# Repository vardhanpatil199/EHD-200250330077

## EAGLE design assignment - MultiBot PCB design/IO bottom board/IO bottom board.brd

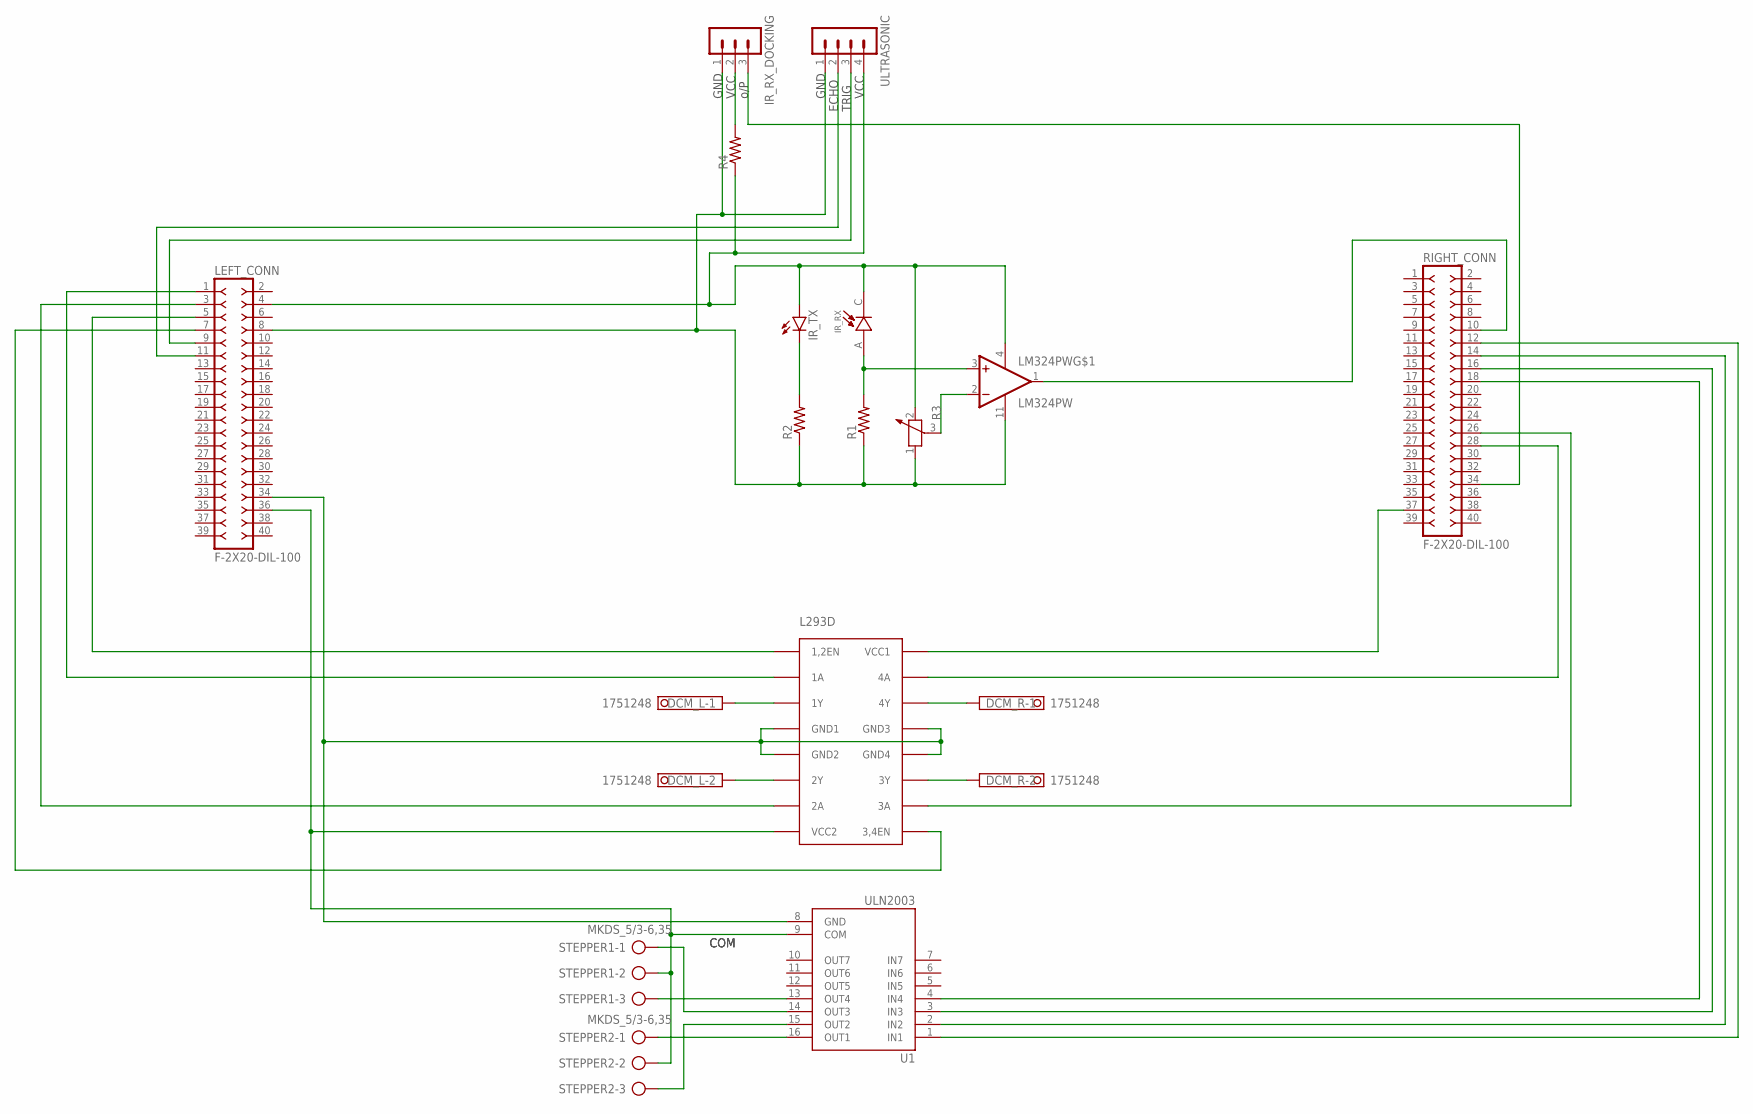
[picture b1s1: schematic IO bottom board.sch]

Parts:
DCM_L: 1751248
DCM_R: 1751248
IR_RX: BPV10; XDCR_BPV10
IR_RX_DOCKING: MA03-1
IR_TX: SFH482
L293D: L293D; DIL16
LEFT_CONN: F-2X20-DIL-100; DIL-100-2X20
LM324PW: LM324PW; SOP65P640X120-14N
R1, R2, R4: R-US_0204/5; 0204/5
R3: POTENTIOMETER_PT-10; PT-10
RIGHT_CONN: F-2X20-DIL-100; DIL-100-2X20
STEPPER1, STEPPER2: MKDS_5/3-6,35; MKDS_5/3-635
U1: ULN2003; DIP762W46P254L1969H533Q16
ULTRASONIC: MA04-1

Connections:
unnamed: DCM_L.1, L293D.3 (1Y)
unnamed: DCM_L.2, L293D.6 (2Y)
unnamed: DCM_R.1, L293D.14 (4Y)
unnamed: DCM_R.2, L293D.11 (3Y)
unnamed: LEFT_CONN.11, ULTRASONIC.2
unnamed: LEFT_CONN.9, ULTRASONIC.3
unnamed: IR_RX_DOCKING.2, R4.2
unnamed: L293D.16 (VCC1), RIGHT_CONN.37
unnamed: RIGHT_CONN.12, U1.1 (IN1)
unnamed: RIGHT_CONN.14, U1.2 (IN2)
unnamed: RIGHT_CONN.16, U1.3 (IN3)
unnamed: RIGHT_CONN.18, U1.4 (IN4)
unnamed: STEPPER2.1, U1.16 (OUT1)
unnamed: STEPPER2.3, U1.15 (OUT2)
unnamed: STEPPER1.1, U1.14 (OUT3)
unnamed: STEPPER1.3, U1.13 (OUT4)
unnamed: L293D.8 (VCC2), LEFT_CONN.36, STEPPER1.2, STEPPER2.2, U1.9 (COM)
unnamed: LM324PW.1 (OUT1), RIGHT_CONN.10
unnamed: L293D.4 (GND1), L293D.5 (GND2), L293D.12 (GND4), L293D.13 (GND3), LEFT_CONN.34, U1.8 (GND)
unnamed: IR_RX.C, IR_TX.A, LEFT_CONN.4, LM324PW.4 (VCC), R3.2, R4.1, ULTRASONIC.4
unnamed: IR_TX.K (C), R2.2
unnamed: IR_RX.A, LM324PW.3 (+IN1), R1.2
unnamed: LM324PW.2 (-IN1), R3.3
unnamed: L293D.1 (1,2EN), LEFT_CONN.5
unnamed: L293D.9 (3,4EN), LEFT_CONN.7
unnamed: IR_RX_DOCKING.1, LEFT_CONN.8, LM324PW.11 (GND), R1.1, R2.1, R3.1, ULTRASONIC.1
unnamed: IR_RX_DOCKING.3, RIGHT_CONN.34
unnamed: L293D.2 (1A), LEFT_CONN.1
unnamed: L293D.7 (2A), LEFT_CONN.3
unnamed: L293D.10 (3A), RIGHT_CONN.26
unnamed: L293D.15 (4A), RIGHT_CONN.28

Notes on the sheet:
GND
VCC
o/P
TRIG
ECHO
COM

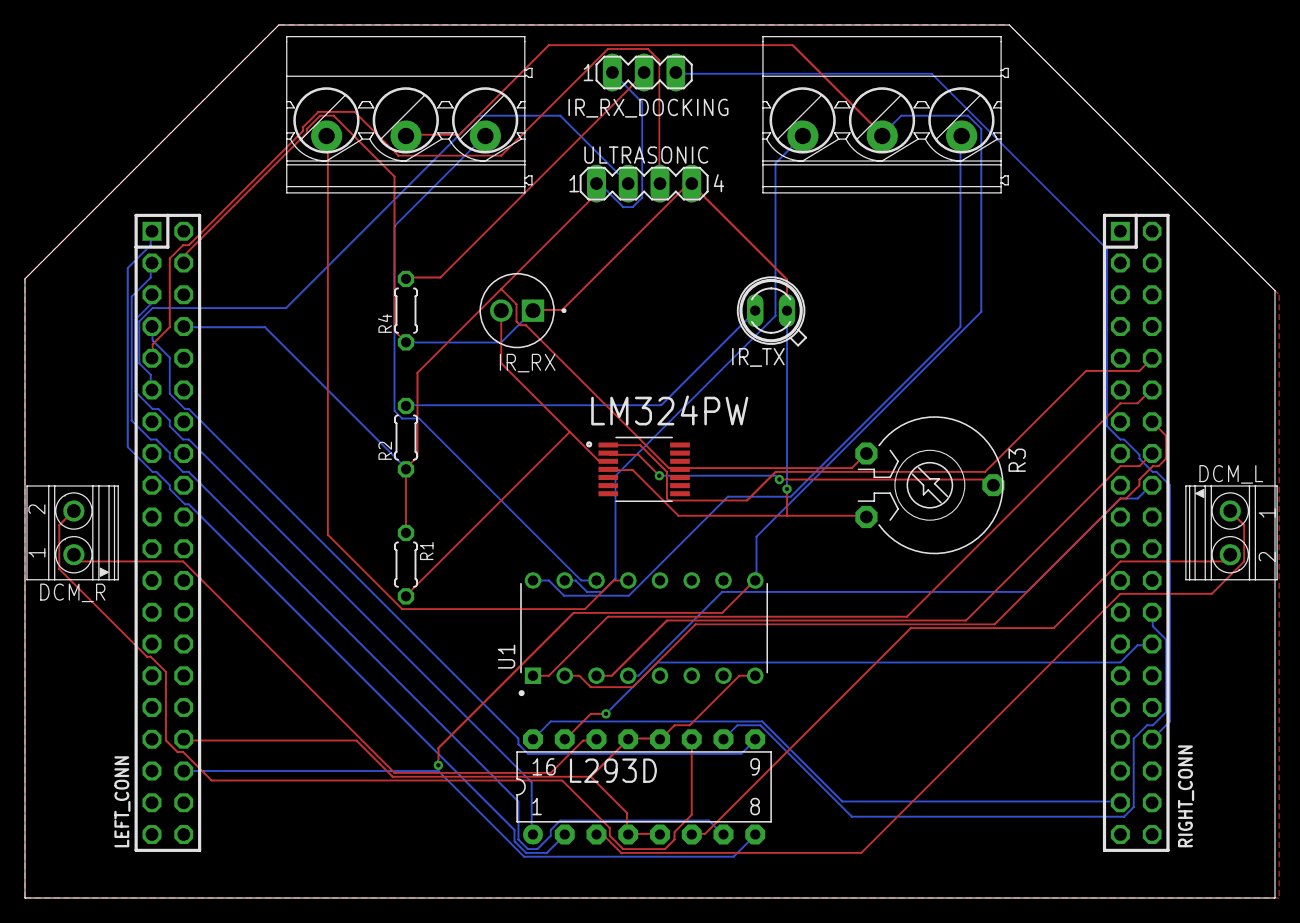
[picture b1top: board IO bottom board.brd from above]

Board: 2 copper layers, 100.0 x 69.8 mm, 17 parts (0 on the bottom side), 31 nets.

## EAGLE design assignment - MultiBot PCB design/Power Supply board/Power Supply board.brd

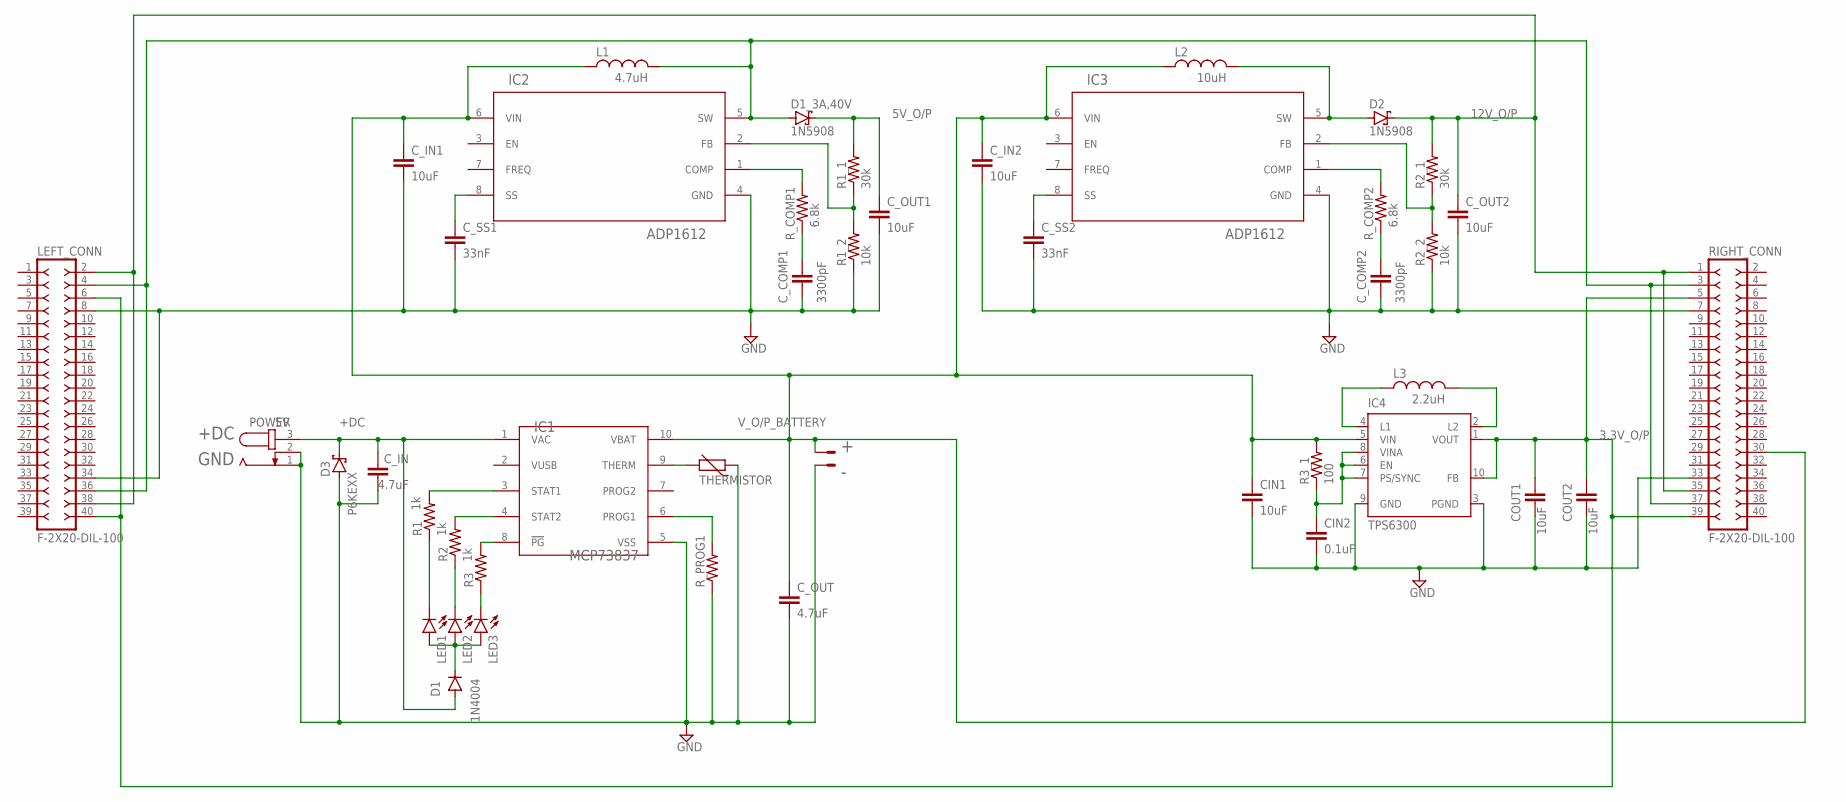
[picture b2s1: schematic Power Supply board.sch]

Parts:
BATT-CHARGING: JST-XH-02-PIN-ROUND-PAD; JST-XH-02-PACKAGE-ROUND-PAD
CIN1: 10uF; C025-024X044
CIN2: 0.1uF; C025-024X044
COUT1, COUT2: 10uF; C025-024X044
C_COMP1, C_COMP2: 3300pF; C025-024X044
C_IN: 4.7uF; C025-024X044
C_IN1, C_IN2: 10uF; C025-024X044
C_OUT: 4.7uF; C025-024X044
C_OUT1, C_OUT2: 10uF; C025-024X044
C_SS1, C_SS2: 33nF; C025-024X044
D1: 1N4004; DO41-10
D1_3A,40V, D2: 1N5908; C4111-15
D3: P6KEXX; CB417-15
IC1: MCP73837; MSOP10_MC_MCH
IC2, IC3: ADP1612; RM_8_ADI
IC4: TPS6300; DRC-S-PVSON-N10
L1: 4.7uH; 0204/7
L2: 10uH; 0204/7
L3: 2.2uH; 0204/7
LED1, LED2, LED3: LED3MM
LEFT_CONN: F-2X20-DIL-100; DIL-100-2X20
POWER: 5V; SPC4077
R1, R2, R3: 1k; 0204/7
R1_1, R2_1: 30k; 0204/7
R1_2, R2_2: 10k; 0204/7
R3_1: 100; 0204/7
RIGHT_CONN: F-2X20-DIL-100; DIL-100-2X20
R_COMP1, R_COMP2: 6.8k; 0204/7
R_PROG1: R-US_0204/7; 0204/7
THERMISTOR: THERMISTOR-5; R-5

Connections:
3.3V_O/P: COUT1.1, COUT2.1, IC4.1 (VOUT), IC4.10 (FB), LEFT_CONN.6, LEFT_CONN.40, RIGHT_CONN.5, RIGHT_CONN.39
5V_O/P: C_OUT1.1, D1_3A,40V.C, R1_1.2
12V_O/P: C_OUT2.1, D2.C, LEFT_CONN.2, LEFT_CONN.38, R2_1.2, RIGHT_CONN.1, RIGHT_CONN.35
+DC: C_IN.1, D1.A, D3.C, IC1.1 (VAC), POWER.3
GND: BATT-CHARGING.2, CIN1.2, CIN2.2, COUT1.2, COUT2.2, C_COMP1.2, C_COMP2.2, C_IN.2, C_IN1.2, C_IN2.2, C_OUT.2, C_OUT1.2, C_OUT2.2, C_SS1.2, C_SS2.2, D3.A, IC1.5 (VSS), IC2.4 (GND), IC3.4 (GND), IC4.3 (PGND), IC4.9 (GND), LEFT_CONN.8, LEFT_CONN.34, POWER.1, POWER.2, R1_2.1, R2_2.1, RIGHT_CONN.7, RIGHT_CONN.33, R_PROG1.1, THERMISTOR.1
unnamed: IC4.4 (L1), L3.1
unnamed: D1_3A,40V.A, IC2.5 (SW), L1.2, LEFT_CONN.4, LEFT_CONN.36, RIGHT_CONN.3, RIGHT_CONN.37
unnamed: IC2.2 (FB), R1_1.1, R1_2.2
unnamed: IC2.1 (COMP), R_COMP1.2
unnamed: C_COMP1.1, R_COMP1.1
unnamed: IC4.2 (L2), L3.2
unnamed: D2.A, IC3.5 (SW), L2.2
unnamed: IC1.6 (PROG1), R_PROG1.2
unnamed: IC3.2 (FB), R2_1.1, R2_2.2
unnamed: C_SS1.1, IC2.8 (SS)
unnamed: IC3.1 (COMP), R_COMP2.2
unnamed: C_COMP2.1, R_COMP2.1
unnamed: C_SS2.1, IC3.8 (SS)
unnamed: IC1.3 (STAT1), R1.2
unnamed: IC1.4 (STAT2), R2.2
unnamed: CIN2.1, IC4.6 (EN), IC4.7 (PS/SYNC), IC4.8 (VINA), R3_1.1
unnamed: IC1.8 (!PG), R3.2
unnamed: D1.C, LED1.A, LED2.A, LED3.A
unnamed: LED1.K (C), R1.1
unnamed: LED2.K (C), R2.1
unnamed: LED3.K (C), R3.1
unnamed: IC1.9 (THERM), THERMISTOR.2
V_O/P_BATTERY: BATT-CHARGING.1, CIN1.1, C_IN1.1, C_IN2.1, C_OUT.1, IC1.10 (VBAT), IC2.6 (VIN), IC3.6 (VIN), IC4.5 (VIN), L1.1, L2.1, R3_1.2, RIGHT_CONN.30

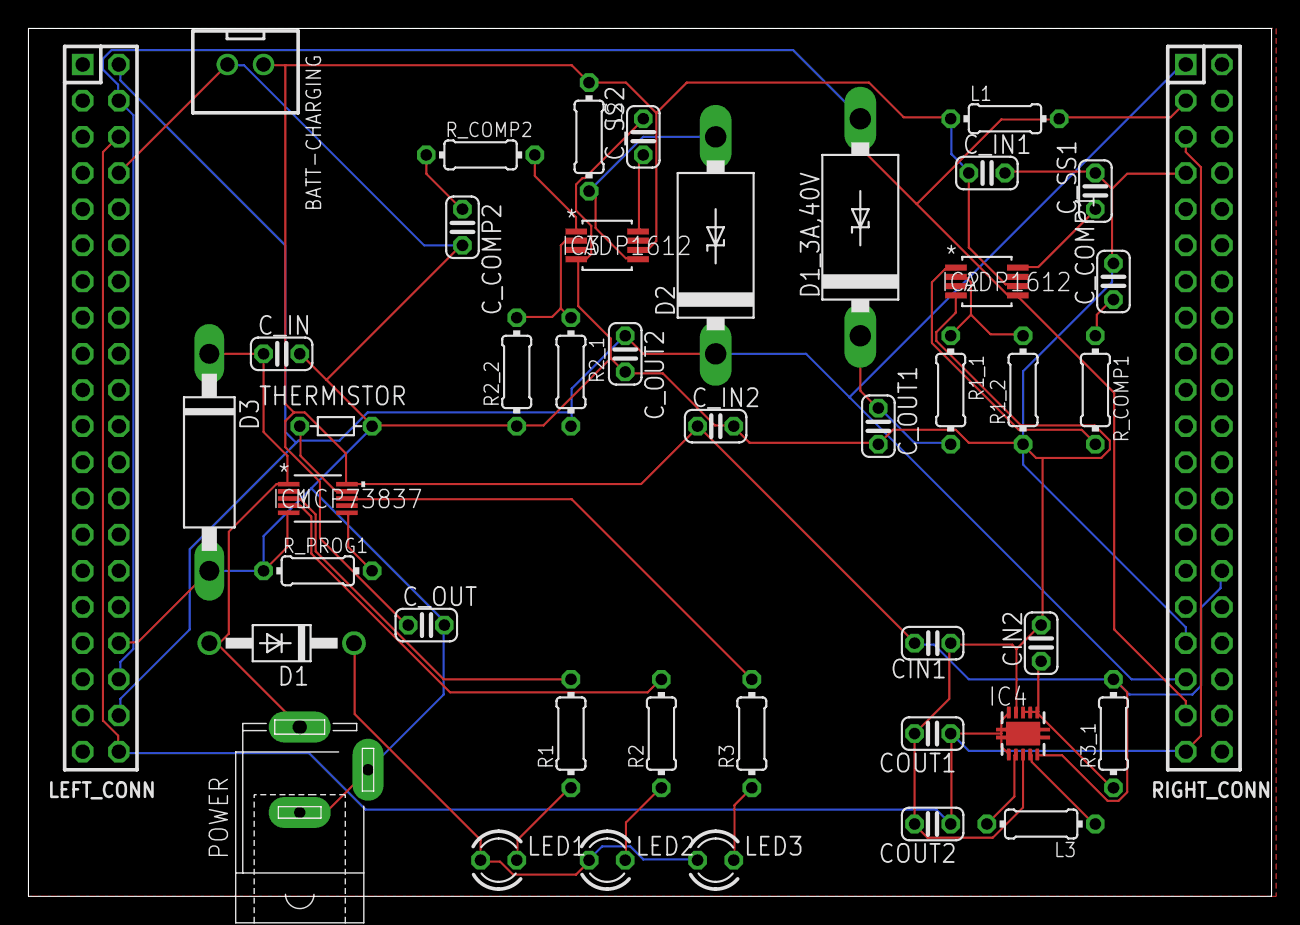
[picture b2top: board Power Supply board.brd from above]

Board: 2 copper layers, 87.3 x 61.0 mm, 44 parts (0 on the bottom side), 28 nets.

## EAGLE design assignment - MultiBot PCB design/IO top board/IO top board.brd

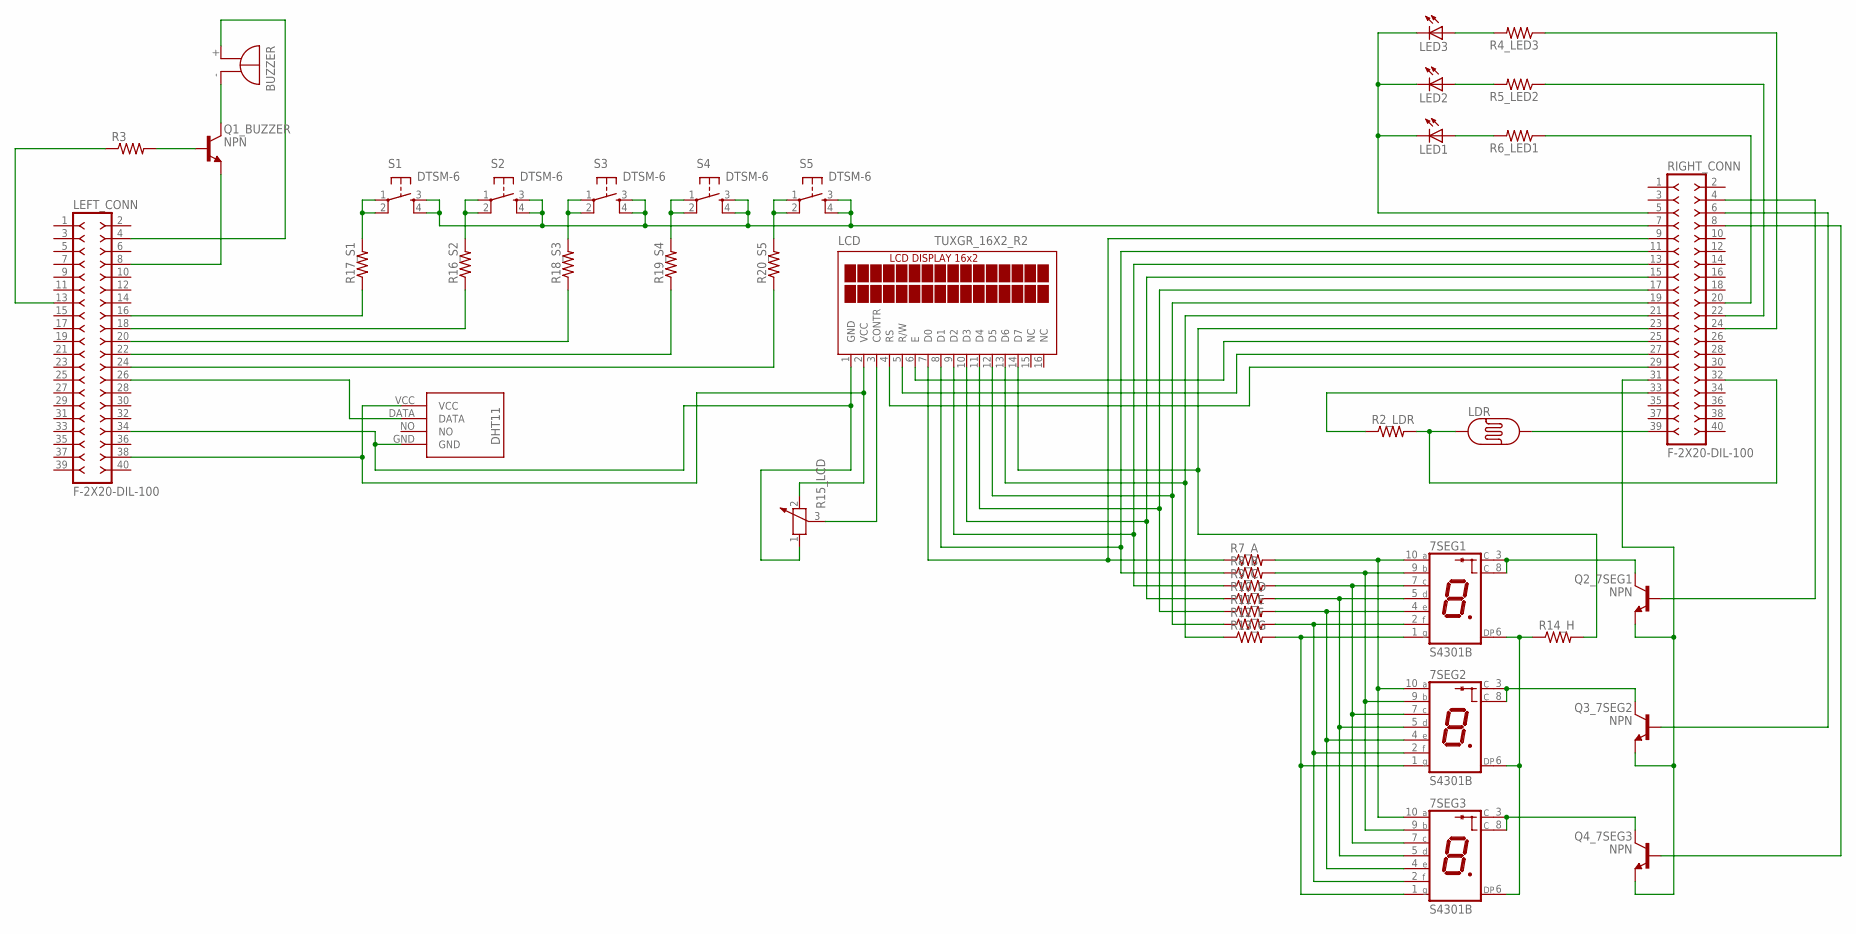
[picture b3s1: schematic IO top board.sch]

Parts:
7SEG1, 7SEG2, 7SEG3: S4301B
BUZZER: EB2209A
LCD: TUXGR_16X2_R2
LDR: PHOTOCELLONB; ON_BOARD
LED1, LED2, LED3: LED_ELD260; LED_LD260
LEFT_CONN: F-2X20-DIL-100; DIL-100-2X20
Q1_BUZZER, Q2_7SEG1, Q3_7SEG2, Q4_7SEG3: NPN; SC70
R2_LDR, R3, R4_LED3, R5_LED2, R6_LED1, R7_A, R8_B, R9_C, R10_D, R11_E, R12_F, R13_G, R14_H, R16_S2, R17_S1, R18_S3, R19_S4, R20_S5: R-US_0204/5; 0204/5
R15_LCD: POTENTIOMETER_PT-10; PT-10
RIGHT_CONN: F-2X20-DIL-100; DIL-100-2X20
S1, S2, S3, S4, S5: DTSM-6
U$1: DHT11-PION.

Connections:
unnamed: LDR.1, R2_LDR.2, RIGHT_CONN.32
unnamed: R2_LDR.1, RIGHT_CONN.33
unnamed: LDR.2, RIGHT_CONN.39
unnamed: LCD.2 (VCC), LEFT_CONN.38, R15_LCD.2, U$1.VCC
unnamed: LCD.1 (GND), LEFT_CONN.34, R15_LCD.1, U$1.GND
unnamed: LEFT_CONN.26, U$1.DATA
unnamed: Q1_BUZZER.2 (B), R3.2
unnamed: BUZZER.-, Q1_BUZZER.3 (C)
unnamed: BUZZER.+, LEFT_CONN.4
unnamed: LEFT_CONN.8, Q1_BUZZER.1 (E)
unnamed: LED1.A, R6_LED1.2
unnamed: LED2.A, R5_LED2.2
unnamed: LED3.A, R4_LED3.2
unnamed: LEFT_CONN.16, R17_S1.1
unnamed: LED1.K (C), LED2.K (C), LED3.K (C), RIGHT_CONN.5
unnamed: R4_LED3.1, RIGHT_CONN.24
unnamed: R5_LED2.1, RIGHT_CONN.22
unnamed: R6_LED1.1, RIGHT_CONN.20
unnamed: 7SEG1.6 (DP), 7SEG2.6 (DP), 7SEG3.6 (DP), R14_H.1
unnamed: 7SEG1.1 (G), 7SEG2.1 (G), 7SEG3.1 (G), R13_G.2
unnamed: Q2_7SEG1.2 (B), RIGHT_CONN.4
unnamed: LCD.7 (D0), R7_A.1, RIGHT_CONN.9
unnamed: 7SEG1.10 (A), 7SEG2.10 (A), 7SEG3.10 (A), R7_A.2
unnamed: 7SEG1.9 (B), 7SEG2.9 (B), 7SEG3.9 (B), R8_B.2
unnamed: 7SEG1.7 (C), 7SEG2.7 (C), 7SEG3.7 (C), R9_C.2
unnamed: 7SEG1.5 (D), 7SEG2.5 (D), 7SEG3.5 (D), R10_D.2
unnamed: 7SEG1.4 (E), 7SEG2.4 (E), 7SEG3.4 (E), R11_E.2
unnamed: 7SEG1.2 (F), 7SEG2.2 (F), 7SEG3.2 (F), R12_F.2
unnamed: LCD.8 (D1), R8_B.1, RIGHT_CONN.11
unnamed: LCD.9 (D2), R9_C.1, RIGHT_CONN.13
unnamed: LCD.10 (D3), R10_D.1, RIGHT_CONN.15
unnamed: LCD.11 (D4), R11_E.1, RIGHT_CONN.17
unnamed: LCD.12 (D5), R12_F.1, RIGHT_CONN.19
unnamed: LCD.13 (D6), R13_G.1, RIGHT_CONN.21
unnamed: LCD.14 (D7), R14_H.2, RIGHT_CONN.23
unnamed: 7SEG1.3 (C), 7SEG1.8 (C), Q2_7SEG1.3 (C)
unnamed: R17_S1.2, S1.1, S1.2
unnamed: LCD.3 (CONTR), R15_LCD.3
unnamed: 7SEG2.3 (C), 7SEG2.8 (C), Q3_7SEG2.3 (C)
unnamed: LCD.4 (RS), RIGHT_CONN.29
unnamed: R16_S2.2, S2.1, S2.2
unnamed: LCD.6 (E), RIGHT_CONN.25
unnamed: LCD.5 (R/W), RIGHT_CONN.27
unnamed: Q2_7SEG1.1 (E), Q3_7SEG2.1 (E), Q4_7SEG3.1 (E), RIGHT_CONN.31
unnamed: 7SEG3.3 (C), 7SEG3.8 (C), Q4_7SEG3.3 (C)
unnamed: R18_S3.2, S3.1, S3.2
unnamed: R19_S4.2, S4.1, S4.2
unnamed: R20_S5.2, S5.1, S5.2
unnamed: LEFT_CONN.18, R16_S2.1
unnamed: LEFT_CONN.20, R18_S3.1
unnamed: LEFT_CONN.22, R19_S4.1
unnamed: LEFT_CONN.24, R20_S5.1
unnamed: LEFT_CONN.13, R3.1
unnamed: Q3_7SEG2.2 (B), RIGHT_CONN.6
unnamed: Q4_7SEG3.2 (B), RIGHT_CONN.8
unnamed: RIGHT_CONN.7, S1.3, S1.4, S2.3, S2.4, S3.3, S3.4, S4.3, S4.4, S5.3, S5.4

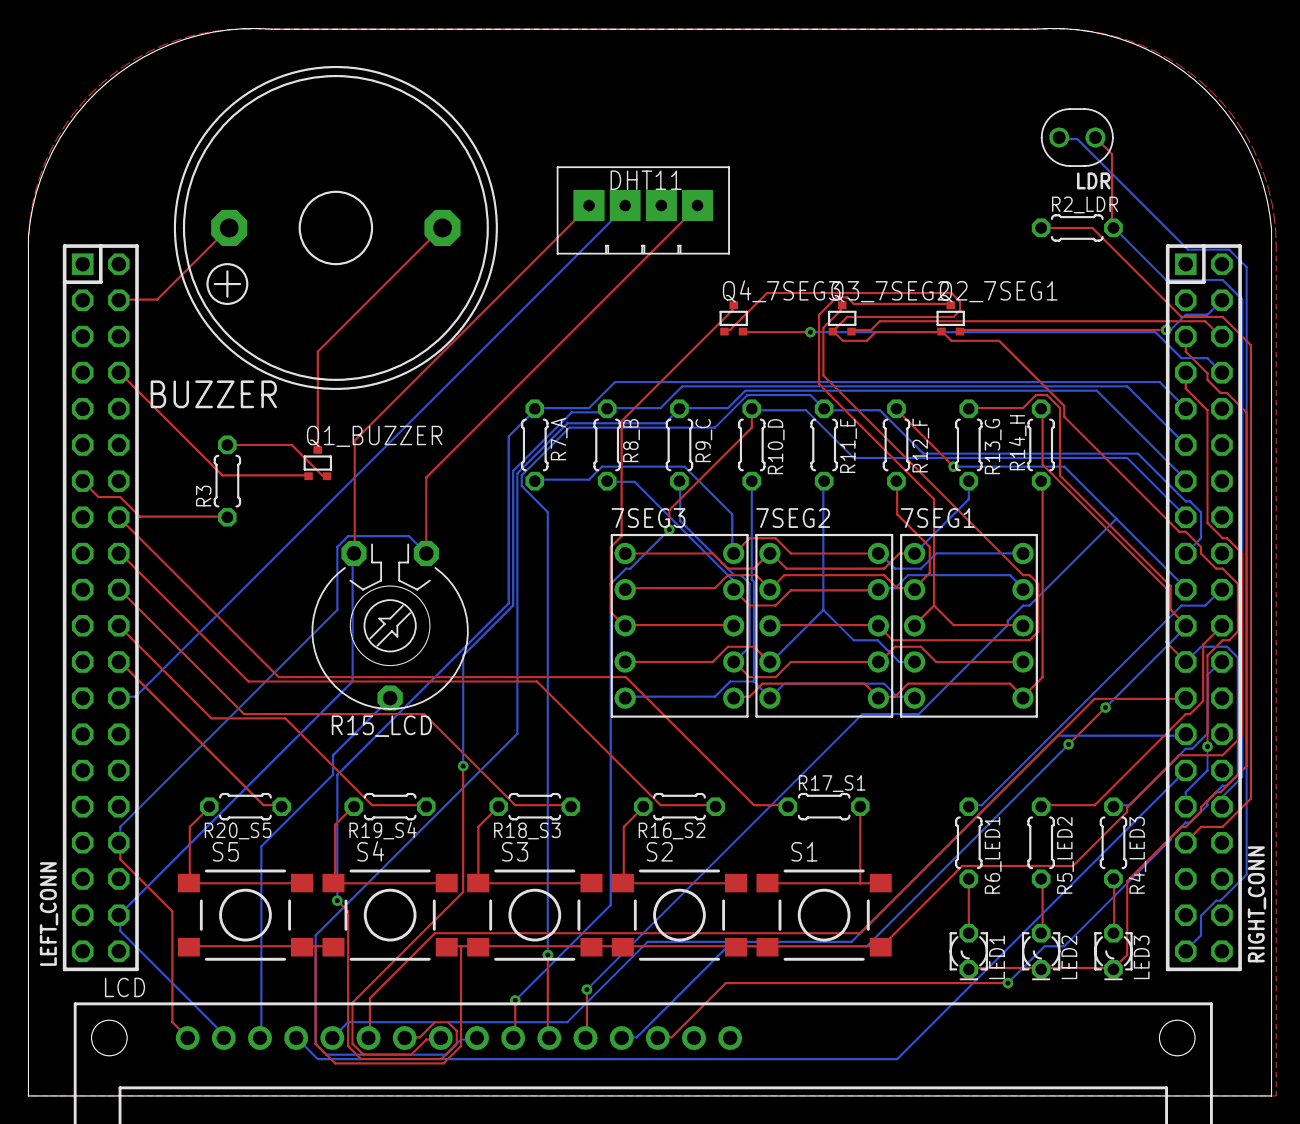
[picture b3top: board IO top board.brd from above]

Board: 2 copper layers, 87.3 x 75.0 mm, 40 parts (0 on the bottom side), 56 nets.

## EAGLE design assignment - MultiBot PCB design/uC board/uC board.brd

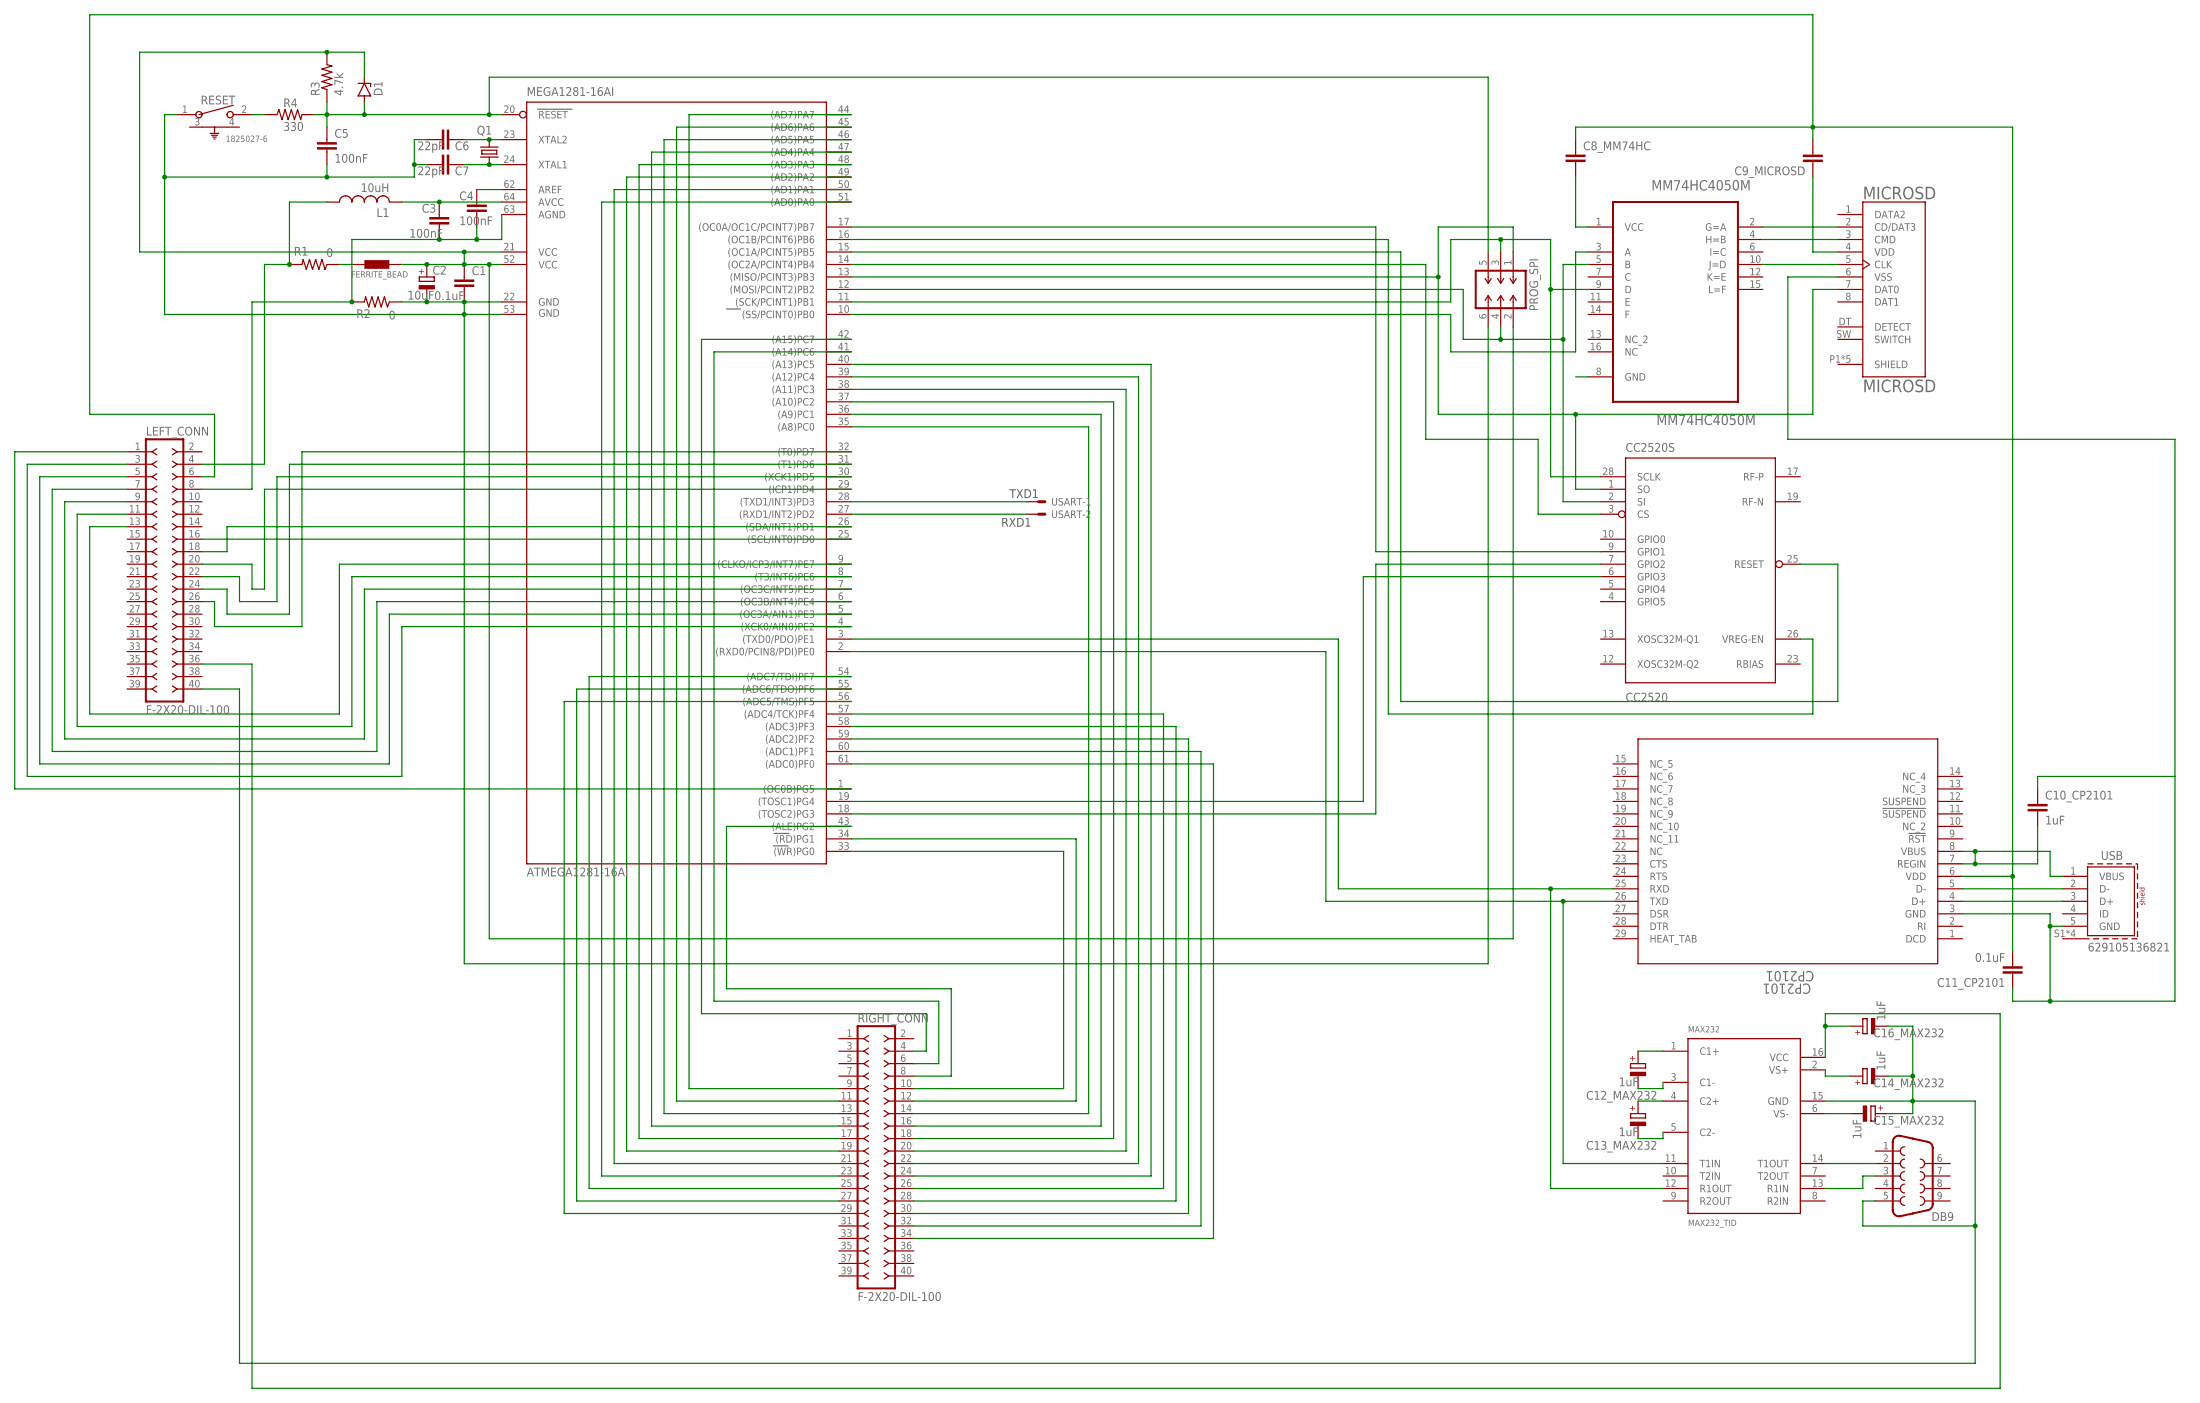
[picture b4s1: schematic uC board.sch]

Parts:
C1: 0.1uF; C0805K
C2: 10uF; E5-10,5
C3, C4, C5: 100nF; C025-024X044
C6, C7: 22pF; C025-024X044
C8_MM74HC, C9_MICROSD: C-EUC1210; C1210
C10_CP2101: 1uF; C1210
C11_CP2101: 0.1uF; C1210
C12_MAX232, C13_MAX232, C14_MAX232, C15_MAX232, C16_MAX232: 1uF; E5-10,5
CC2520: CC2520; QFN50P500X500X100-29N
CP2101: CP2101; MLP28_SIL
D1: ZENER-DIODEDO34-7; DO34Z7
DB9: DB9MALE; DB9_MALE
FERRITE_BEAD: BLM15HB121SN1; 0402
L1: 10uH; 0204/7
LEFT_CONN: F-2X20-DIL-100; DIL-100-2X20
MAX232: MAX232_TID; R-PDSO-G16
MEGA1281-16AI: ATMEGA1281-16AI; TQFP64
MICROSD: MICROSD; MOLEX_503182-1852
MM74HC4050M: MM74HC4050M; SOIC127P600X175-16N
PROG_SPI: M-2X03-DIL-2MM_M; DIL-2MM-2X03_M
Q1: CRYSTALHC49S; HC49/S
R1, R2: 0; 0204/5
R3: 4.7k; 0204/5
R4: 330; 0204/5
RESET: 1825027-6; SW2_1825027-B
RIGHT_CONN: F-2X20-DIL-100; DIL-100-2X20
USART: 332-02
USB: 629105136821

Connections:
AGND: CC2520.29 (AGND)
AVDD: CC2520.11 (AVDD), CC2520.14 (AVDD), CC2520.16 (AVDD), CC2520.20 (AVDD), CC2520.22 (AVDD)
AVDD-GUARD: CC2520.24 (AVDD-GUARD)
DCOUPL: CC2520.27 (DCOUPL)
DVDD: CC2520.8 (DVDD)
unnamed: C1.1, C2.+, D1.C, FERRITE_BEAD.1, MEGA1281-16AI.21 (VCC), MEGA1281-16AI.52 (VCC1), PROG_SPI.2, R3.2
unnamed: CC2520.1 (SO), MEGA1281-16AI.13 ((MISO/PCINT3)PB3), MICROSD.7 (DAT0), PROG_SPI.1
unnamed: C3.1, L1.2, MEGA1281-16AI.64 (AVCC)
unnamed: C4.1, MEGA1281-16AI.62 (AREF)
unnamed: C3.2, C4.2, LEFT_CONN.8, MEGA1281-16AI.63 (AGND), R2.2
unnamed: FERRITE_BEAD.2, R1.1
unnamed: L1.1, LEFT_CONN.4, R1.2
unnamed: C5.1, D1.A, MEGA1281-16AI.20 (RESET), PROG_SPI.5, R3.1, R4.2
unnamed: R4.1, RESET.2
unnamed: C6.2, MEGA1281-16AI.23 (XTAL2), Q1.2
unnamed: C7.2, MEGA1281-16AI.24 (XTAL1), Q1.1
unnamed: CP2101.26 (TXD), MAX232.11 (T1IN), MEGA1281-16AI.2 ((RXD0/PCIN8/PDI)PE0)
unnamed: CC2520.28 (SCLK), MEGA1281-16AI.11 ((SCK/PCINT1)PB1), MM74HC4050M.9 (D), PROG_SPI.3
unnamed: CC2520.2 (SI), MEGA1281-16AI.12 ((MOSI/PCINT2)PB2), MM74HC4050M.5 (B), PROG_SPI.4
unnamed: MICROSD.5 (CLK), MM74HC4050M.10 (J=D)
unnamed: MEGA1281-16AI.10 ((SS/PCINT0)PB0), MM74HC4050M.3 (A)
unnamed: MICROSD.3 (CMD), MM74HC4050M.4 (H=B)
unnamed: MICROSD.2 (CD/DAT3), MM74HC4050M.2 (G=A)
unnamed: C9_MICROSD.1, MICROSD.4 (VDD)
unnamed: C10_CP2101.1, C11_CP2101.1, CP2101.3 (GND), MICROSD.6 (VSS), USB.5 (GND)
unnamed: C1.2, C2.-, C5.2, C6.1, C7.1, MEGA1281-16AI.22 (GND), MEGA1281-16AI.53 (GND1), PROG_SPI.6, R2.1, RESET.1
unnamed: C8_MM74HC.2, MM74HC4050M.1 (VCC)
unnamed: CC2520.3 (CS), MEGA1281-16AI.14 ((OC2A/PCINT4)PB4)
unnamed: CC2520.25 (RESET), MEGA1281-16AI.15 ((OC1A/PCINT5)PB5)
unnamed: CC2520.26 (VREG-EN), MEGA1281-16AI.16 ((OC1B/PCINT6)PB6)
unnamed: CC2520.9 (GPIO1), MEGA1281-16AI.17 ((OC0A/OC1C/PCINT7)PB7)
unnamed: CC2520.7 (GPIO2), MEGA1281-16AI.18 ((TOSC2)PG3)
unnamed: CC2520.6 (GPIO3), MEGA1281-16AI.19 ((TOSC1)PG4)
unnamed: MEGA1281-16AI.28 ((TXD1/INT3)PD3), USART.1
unnamed: C14_MAX232.-, C15_MAX232.+, C16_MAX232.-, DB9.5, LEFT_CONN.40, MAX232.15 (GND)
unnamed: C10_CP2101.2, CP2101.7 (REGIN), CP2101.8 (VBUS), USB.1 (VBUS)
unnamed: CP2101.5 (D-), USB.2 (D-)
unnamed: CP2101.4 (D+), USB.3 (D+)
unnamed: MEGA1281-16AI.27 ((RXD1/INT2)PD2), USART.2
unnamed: C8_MM74HC.1, C9_MICROSD.2, C11_CP2101.2, CP2101.6 (VDD), LEFT_CONN.6
unnamed: CP2101.25 (RXD), MAX232.12 (R1OUT), MEGA1281-16AI.3 ((TXD0/PDO)PE1)
unnamed: C13_MAX232.+, MAX232.4 (C2+)
unnamed: C12_MAX232.+, MAX232.1 (C1+)
unnamed: C12_MAX232.-, MAX232.3 (C1-)
unnamed: C13_MAX232.-, MAX232.5 (C2-)
unnamed: C14_MAX232.+, MAX232.2 (VS+)
unnamed: C15_MAX232.-, MAX232.6 (VS-)
unnamed: C16_MAX232.+, LEFT_CONN.36, MAX232.16 (VCC)
unnamed: DB9.2, MAX232.14 (T1OUT)
unnamed: DB9.3, MAX232.13 (R1IN)
unnamed: LEFT_CONN.1, MEGA1281-16AI.1 ((OC0B)PG5)
unnamed: LEFT_CONN.3, MEGA1281-16AI.4 ((XCK0/AIN0)PE2)
unnamed: LEFT_CONN.5, MEGA1281-16AI.5 ((OC3A/AIN1)PE3)
unnamed: LEFT_CONN.7, MEGA1281-16AI.6 ((OC3B/INT4)PE4)
unnamed: LEFT_CONN.9, MEGA1281-16AI.7 ((OC3C/INT5)PE5)
unnamed: LEFT_CONN.11, MEGA1281-16AI.8 ((T3/INT6)PE6)
unnamed: LEFT_CONN.13, MEGA1281-16AI.9 ((CLKO/ICP3/INT7)PE7)
unnamed: LEFT_CONN.16, MEGA1281-16AI.25 ((SCL/INT0)PD0)
unnamed: LEFT_CONN.18, MEGA1281-16AI.26 ((SDA/INT1)PD1)
unnamed: LEFT_CONN.20, MEGA1281-16AI.29 ((ICP1)PD4)
unnamed: LEFT_CONN.22, MEGA1281-16AI.30 ((XCK1)PD5)
unnamed: LEFT_CONN.24, MEGA1281-16AI.31 ((T1)PD6)
unnamed: LEFT_CONN.26, MEGA1281-16AI.32 ((T0)PD7)
unnamed: MEGA1281-16AI.41 ((A14)PC6), RIGHT_CONN.6
unnamed: MEGA1281-16AI.42 ((A15)PC7), RIGHT_CONN.4
unnamed: MEGA1281-16AI.43 ((ALE)PG2), RIGHT_CONN.8
unnamed: MEGA1281-16AI.44 ((AD7)PA7), RIGHT_CONN.9
unnamed: MEGA1281-16AI.45 ((AD6)PA6), RIGHT_CONN.11
unnamed: MEGA1281-16AI.46 ((AD5)PA5), RIGHT_CONN.13
unnamed: MEGA1281-16AI.47 ((AD4)PA4), RIGHT_CONN.15
unnamed: MEGA1281-16AI.48 ((AD3)PA3), RIGHT_CONN.17
unnamed: MEGA1281-16AI.49 ((AD2)PA2), RIGHT_CONN.19
unnamed: MEGA1281-16AI.50 ((AD1)PA1), RIGHT_CONN.21
unnamed: MEGA1281-16AI.51 ((AD0)PA0), RIGHT_CONN.23
unnamed: MEGA1281-16AI.54 ((ADC7/TDI)PF7), RIGHT_CONN.25
unnamed: MEGA1281-16AI.55 ((ADC6/TDO)PF6), RIGHT_CONN.27
unnamed: MEGA1281-16AI.56 ((ADC5/TMS)PF5), RIGHT_CONN.29
unnamed: MEGA1281-16AI.33 ((WR)PG0), RIGHT_CONN.10
unnamed: MEGA1281-16AI.34 ((RD)PG1), RIGHT_CONN.12
unnamed: MEGA1281-16AI.35 ((A8)PC0), RIGHT_CONN.14
unnamed: MEGA1281-16AI.36 ((A9)PC1), RIGHT_CONN.16
unnamed: MEGA1281-16AI.37 ((A10)PC2), RIGHT_CONN.18
unnamed: MEGA1281-16AI.38 ((A11)PC3), RIGHT_CONN.20
unnamed: MEGA1281-16AI.39 ((A12)PC4), RIGHT_CONN.22
unnamed: MEGA1281-16AI.40 ((A13)PC5), RIGHT_CONN.24
unnamed: MEGA1281-16AI.57 ((ADC4/TCK)PF4), RIGHT_CONN.26
unnamed: MEGA1281-16AI.58 ((ADC3)PF3), RIGHT_CONN.28
unnamed: MEGA1281-16AI.59 ((ADC2)PF2), RIGHT_CONN.30
unnamed: MEGA1281-16AI.60 ((ADC1)PF1), RIGHT_CONN.32
unnamed: MEGA1281-16AI.61 ((ADC0)PF0), RIGHT_CONN.34

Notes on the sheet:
TXD1
RXD1

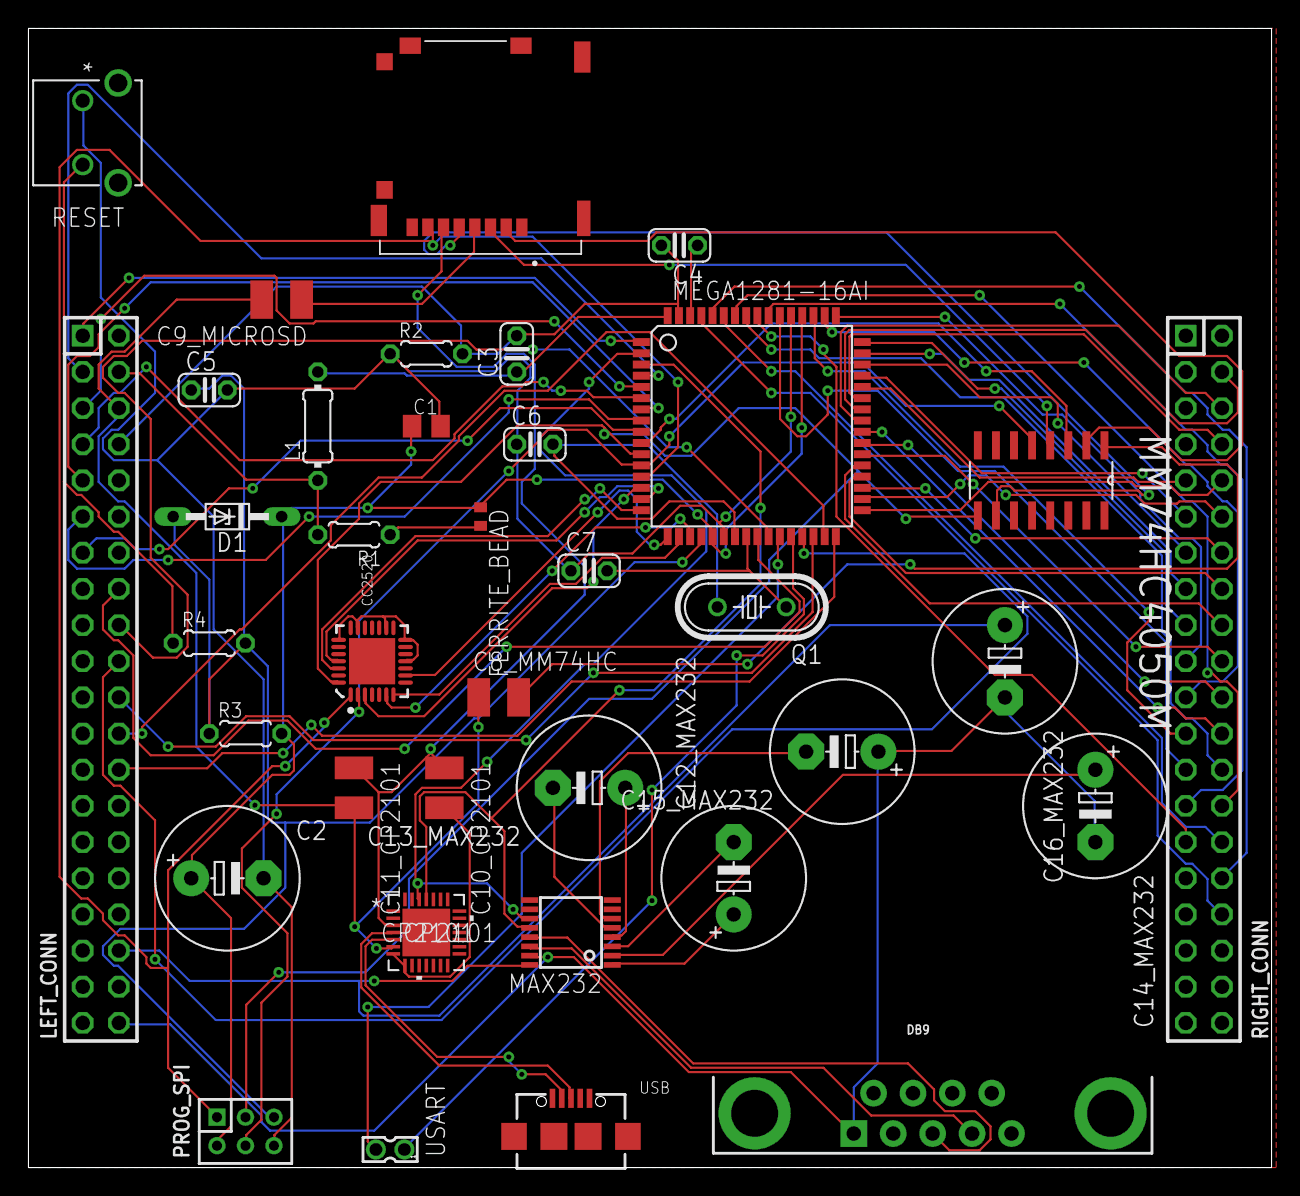
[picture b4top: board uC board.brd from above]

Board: 2 copper layers, 87.3 x 80.0 mm, 37 parts (0 on the bottom side), 86 nets.

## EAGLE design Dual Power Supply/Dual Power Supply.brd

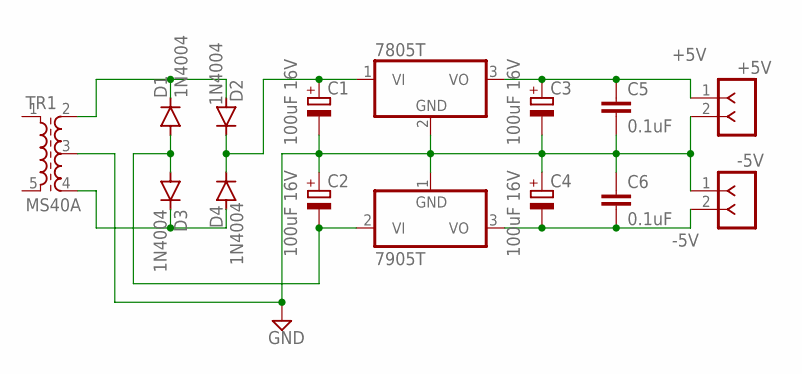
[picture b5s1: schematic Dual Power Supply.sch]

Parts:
7805T: 7805T; TO220H
7905T: 7905T; TO220H
+5V: F-1X02-SIP-100-40Y; SIP-100-02-40Y
-5V: F-1X02-SIP-100-40Y; SIP-100-02-40Y
C1, C2, C3, C4: 100uF 16V; SANYO-OSCON_C6
C5, C6: 0.1uF; C025-024X044
D1, D2, D3, D4: 1N4004; DO41-10
TR1: MS40A; MS40

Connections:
+5V: 7805T.3 (VO), +5V.1, C3.+, C5.1
-5V: 7905T.3 (VO), -5V.2, C4.-, C6.2
GND: 7805T.2 (GND), 7905T.1 (GND), +5V.2, -5V.1, C1.-, C2.+, C3.-, C4.+, C5.2, C6.1, TR1.3
unnamed: D1.C, D2.A, TR1.2
unnamed: D3.C, D4.A, TR1.4
unnamed: 7905T.2 (VI), C2.-, D1.A, D3.A
unnamed: 7805T.1 (VI), C1.+, D2.C, D4.C

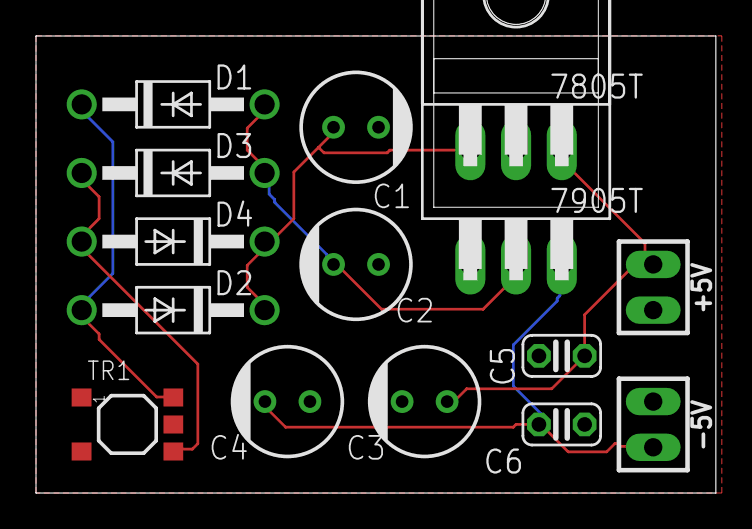
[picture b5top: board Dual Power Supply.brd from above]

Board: 2 copper layers, 37.8 x 25.4 mm, 15 parts (0 on the bottom side), 7 nets.

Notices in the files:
parts and their libraries:
con-headers-jp: Copyright (C) 2008, Bob Starr
Wurth_Connectors_WR-USB: Copyright: Würth Elektronik
SparkFun-Connectors: Licensing: Creative Commons ShareAlike 4.0 International - https://creativecommons.org/licenses/by-sa/4.0
COPYRIGHT: Copyright (C) 2016 Accelerated Designs. All rights reserved
